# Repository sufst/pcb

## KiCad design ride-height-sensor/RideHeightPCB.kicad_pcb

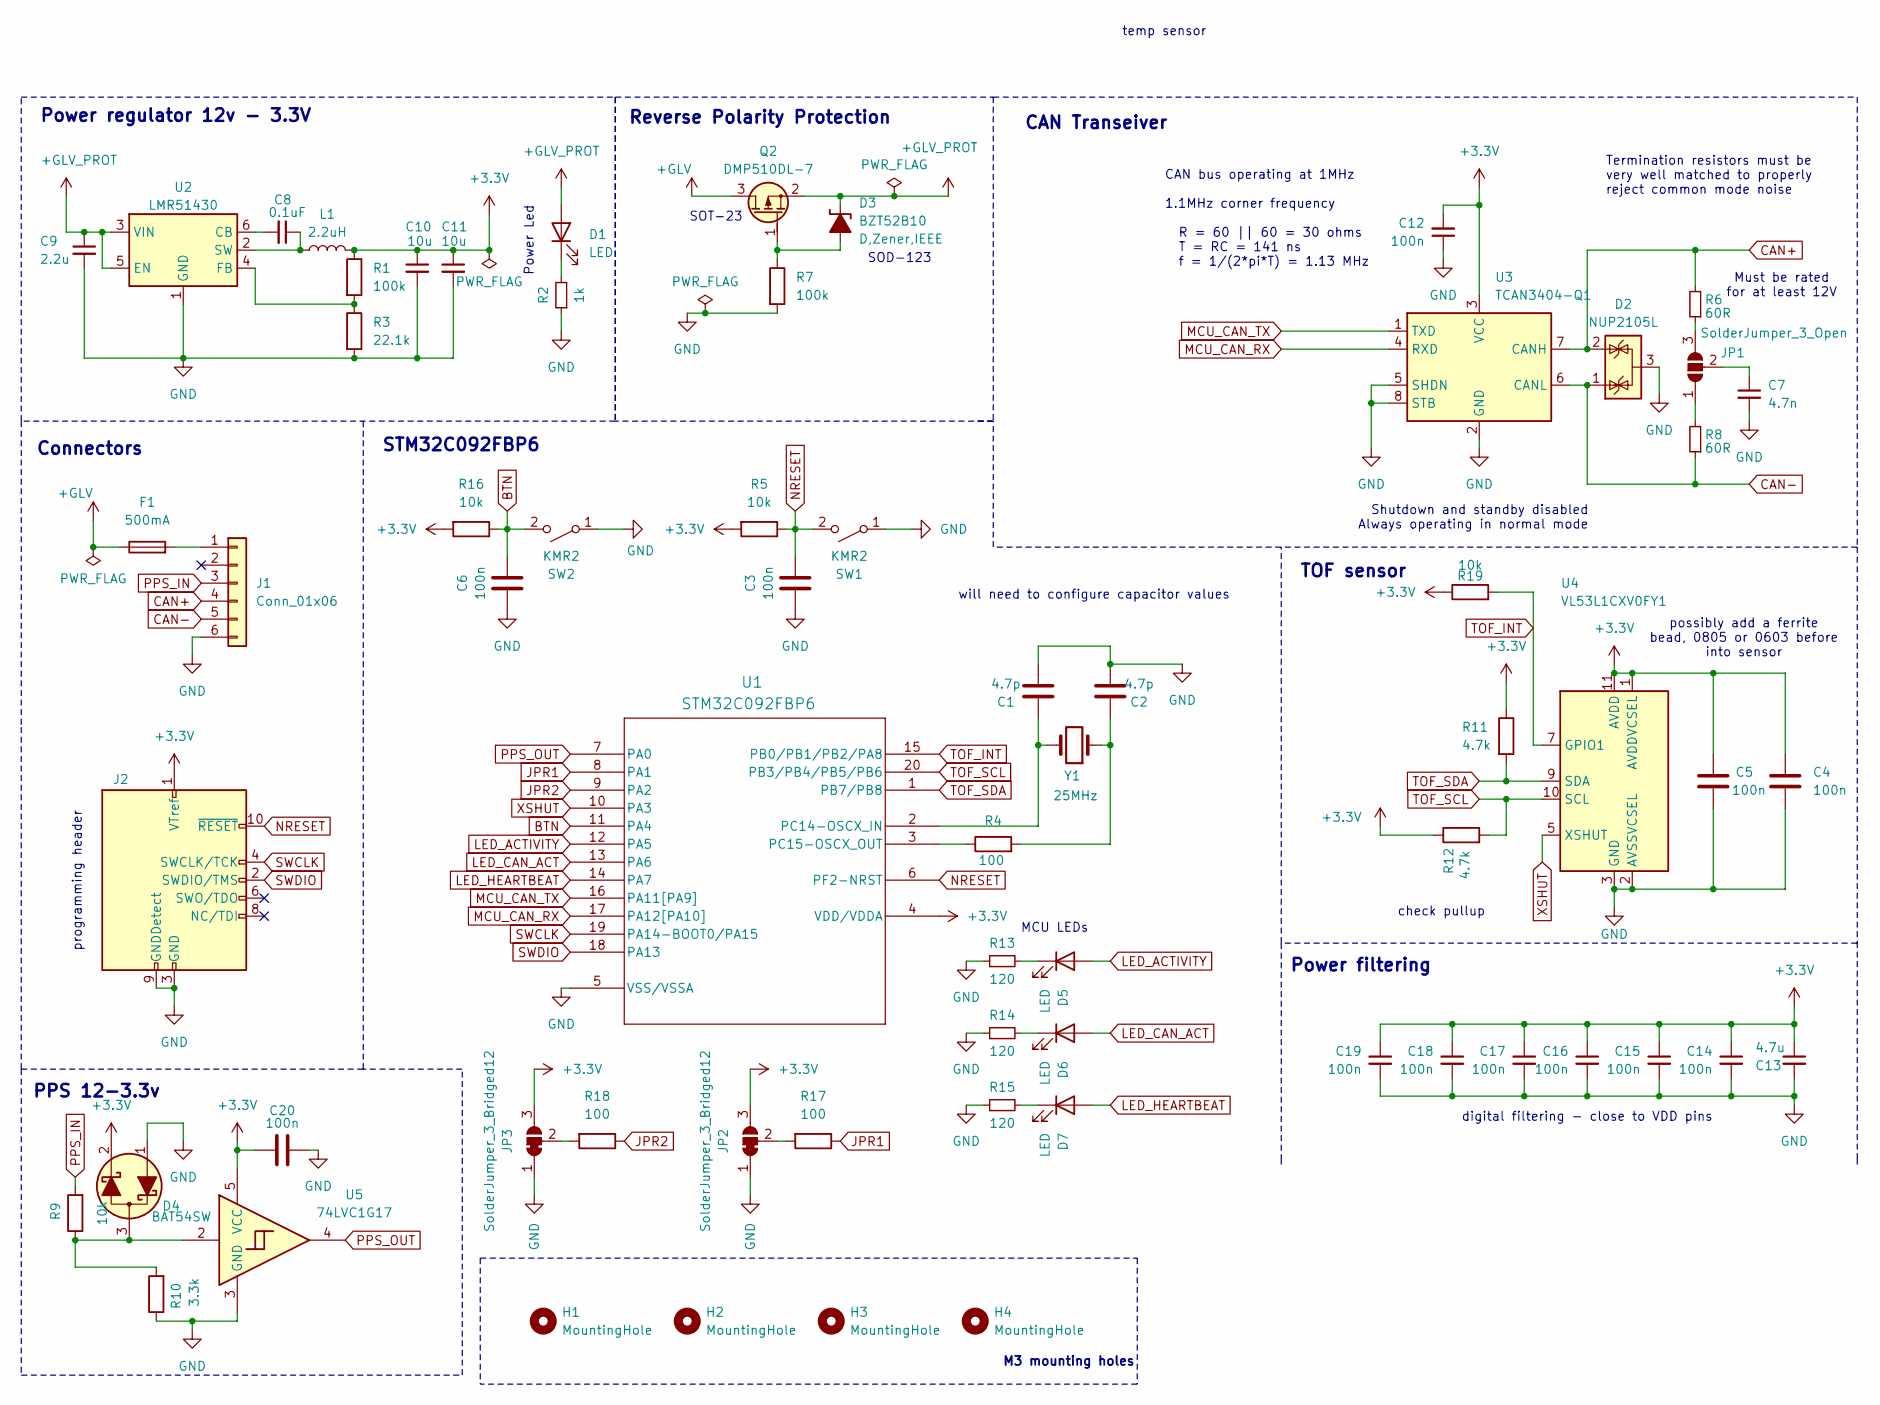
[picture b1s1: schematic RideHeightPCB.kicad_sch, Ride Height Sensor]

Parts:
C1, C2: 4.7p; C_0603_1608Metric_Pad1.08x0.95mm_HandSolder
C3, C4, C5, C6, C12, C14, C15, C16, C17, C18, C19, C20: 100n; C_0603_1608Metric_Pad1.08x0.95mm_HandSolder
C7: 4.7n; C_0603_1608Metric_Pad1.08x0.95mm_HandSolder
C8: 0.1uF; C_0603_1608Metric_Pad1.08x0.95mm_HandSolder
C9: 2.2u; C_0603_1608Metric_Pad1.08x0.95mm_HandSolder
C10: 10u; C_0805_2012Metric_Pad1.18x1.45mm_HandSolder
C11: 10u; C_0603_1608Metric_Pad1.08x0.95mm_HandSolder
C13: 4.7u; C_0603_1608Metric_Pad1.08x0.95mm_HandSolder
D1, D5, D6, D7: LED; LED_0805_2012Metric_Pad1.15x1.40mm_HandSolder
D2: NUP2105L; SOT-23; MPN NUP2105L
D3: BZT52B10; D_SOD-123; MPN BZT52B10
D4: BAT54SW; SOT-323_SC-70
F1: 500mA; Fuse_0603_1608Metric_Pad1.05x0.95mm_HandSolder
H1, H2, H3, H4: MountingHole; MountingHole_3.2mm_M3
J1: Conn_01x06; Molex_Micro-Fit_3.0_43650-0600_1x06_P3.00mm_Horizontal
J2: SHF10501LDSMLC; Mouser Order Number 200-SHF10501LDSMLC
JP1: SolderJumper_3_Open; SolderJumper-3_P1.3mm_Open_RoundedPad1.0x1.5mm
JP2, JP3: SolderJumper_3_Bridged12; SolderJumper-3_P1.3mm_Open_RoundedPad1.0x1.5mm
L1: 2.2uH; L_Coilcraft_XAL4020-XXX; MPN XAL4020-222MEC
Q2: DMP510DL-7; SOT-23
R1, R7: 100k; R_0603_1608Metric_Pad0.98x0.95mm_HandSolder
R2: 1k; R_0603_1608Metric_Pad0.98x0.95mm_HandSolder
R3: 22.1k; R_0603_1608Metric_Pad0.98x0.95mm_HandSolder
R4, R17, R18: 100; R_0603_1608Metric_Pad0.98x0.95mm_HandSolder
R5, R9, R16, R19: 10k; R_0603_1608Metric_Pad0.98x0.95mm_HandSolder
R6, R8: 60R; R_0603_1608Metric_Pad0.98x0.95mm_HandSolder
R10: 3.3k; R_0603_1608Metric_Pad0.98x0.95mm_HandSolder
R11, R12: 4.7k; R_0603_1608Metric_Pad0.98x0.95mm_HandSolder
R13, R14, R15: 120; R_0603_1608Metric_Pad0.98x0.95mm_HandSolder
SW1, SW2: KMR2; SW_Push_1P1T_NO_CK_KMR2; MPN KMR221NG LFS
U1: STM32C092FBP6; TSSOP20_STM
U2: LMR51430; SOT-23-6; MPN LMR51430YDDCR
U3: TCAN3404-Q1; SOT-23-8_Handsoldering; MPN TCAN3404DDFRQ1
U4: VL53L1CXV0FY1; ST_VL53L1x
U5: 74LVC1G17; SOT-353_SC-70-5_Handsoldering
Y1: 25MHz; Resonator_SMD_ECS_ECX-1247Q_1.6x1.2x0.3mm

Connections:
+3.3V: C4.2, C5.2, C10.1, C11.1, C12.2, C13.1, C14.1, C15.1, C16.1, C17.1, C18.1, C19.1, C20.1, D4.2 (K), J2.1 (VTref), JP2.3 (B), JP3.3 (B), L1.2, R1.1, R5.2, R11.1, R12.1, R16.2, R19.1, U1.4 (VDD/VDDA), U3.3 (VCC), U4.1 (AVDDVCSEL), U4.11 (AVDD), U5.5 (VCC)
+GLV: F1.1, Q2.3 (D); also elsewhere on the board
+GLV_PROT: C9.1, D1.2 (A), D3.1 (K-), Q2.2 (S), U2.3 (VIN), U2.5 (EN); also elsewhere on the board
BTN: C6.1, R16.1, SW2.2 (B), U1.11 (PA4)
CAN+: D2.2 (K), J1.4, R6.2, U3.7 (CANH)
CAN-: D2.1 (K), J1.5, R8.1, U3.6 (CANL)
JPR1: R17.1, U1.8 (PA1)
JPR2: R18.1, U1.9 (PA2)
LED_ACTIVITY: D5.2 (A), U1.12 (PA5)
LED_CAN_ACT: D6.2 (A), U1.13 (PA6)
LED_HEARTBEAT: D7.2 (A), U1.14 (PA7)
MCU_CAN_RX: U1.17 (PA12[PA10]), U3.4 (RXD)
MCU_CAN_TX: U1.16 (PA11[PA9]), U3.1 (TXD)
NRESET: C3.1, J2.10 (~RESET), R5.1, SW1.2 (B), U1.6 (PF2-NRST)
unnamed: D1.1 (K), R2.2
unnamed 15: D3.2 (A+), Q2.1 (G), R7.1; also elsewhere on the board
unnamed: D4.3 (C), R9.1, R10.2, U5.2
unnamed: D5.1 (K), R13.2
unnamed: D6.1 (K), R14.2
unnamed: D7.1 (K), R15.2
unnamed: F1.2, J1.1
unnamed: JP1.1 (A), R8.2
unnamed: JP1.3 (B), R6.1
unnamed: C7.1, JP1.2 (C)
unnamed: JP2.2 (C), R17.2
unnamed: JP3.2 (C), R18.2
unnamed: R4.1, U1.3 (PC15-OSCX_OUT)
unnamed: C8.2, U2.6 (CB)
unnamed: R1.2, R3.1, U2.4 (FB)
unnamed: C8.1, L1.1, U2.2 (SW)
PPS_IN: J1.3, R9.2
PPS_OUT: U1.7 (PA0), U5.4
SWCLK: J2.4 (SWCLK/TCK), U1.19 (PA14-BOOT0/PA15)
SWDIO: J2.2 (SWDIO/TMS), U1.18 (PA13)
TOF_INT: R19.2, U1.15 (PB0/PB1/PB2/PA8), U4.7 (GPIO1)
TOF_SCL: R12.2, U1.20 (PB3/PB4/PB5/PB6), U4.10 (SCL)
TOF_SDA: R11.2, U1.1 (PB7/PB8), U4.9 (SDA)
XSHUT: U1.10 (PA3), U4.5 (XSHUT)

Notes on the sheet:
PPS 12-3.3v
SOD-123
Termination resistors must be very well matched to properly reject common mode noise
CAN bus operating at 1MHz 1.1MHz corner frequency R = 60 || 60 = 30 ohms T = RC = 141 ns f = 1/(2*pi*T) = 1.13 MHz
Reverse Polarity Protection
Power filtering
will need to configure capacitor values
STM32C092FBP6
temp sensor
TOF sensor
Power regulator 12v - 3.3V
CAN Transeiver
MCU LEDs
programming header
check pullup
Connectors
SOT-23
digital filtering - close to VDD pins
M3 mounting holes
Must be rated for at least 12V
possibly add a ferrite bead, 0805 or 0603 before into sensor
Shutdown and standby disabled Always operating in normal mode
Power Led

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
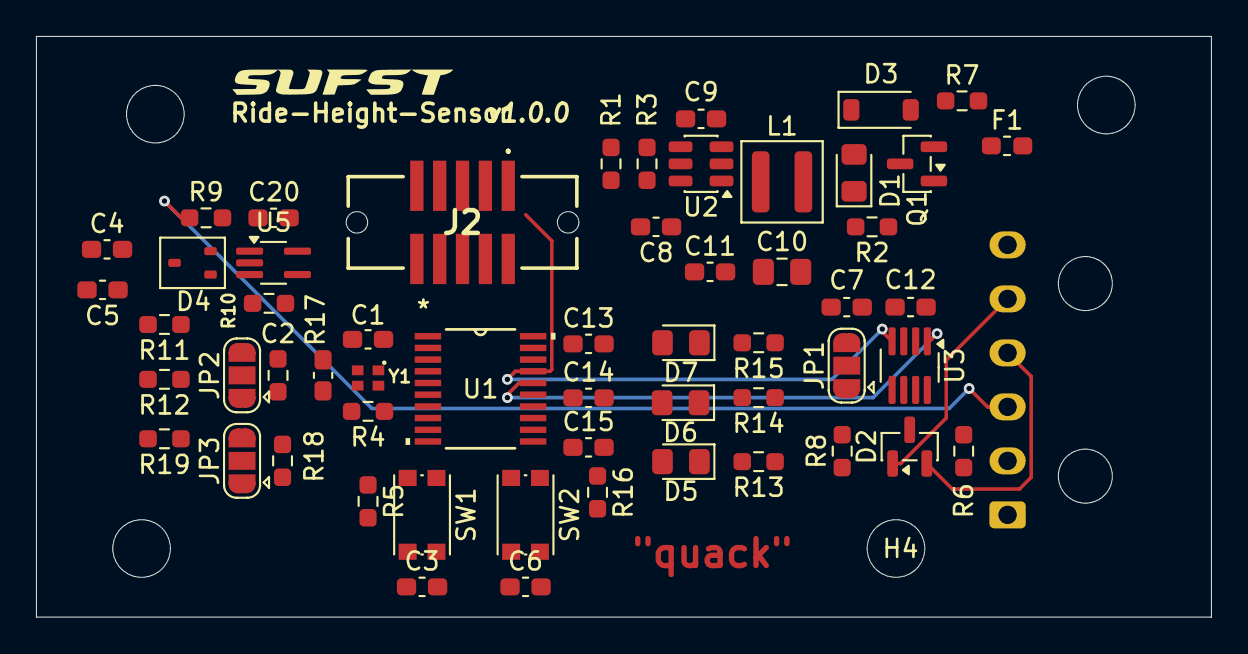
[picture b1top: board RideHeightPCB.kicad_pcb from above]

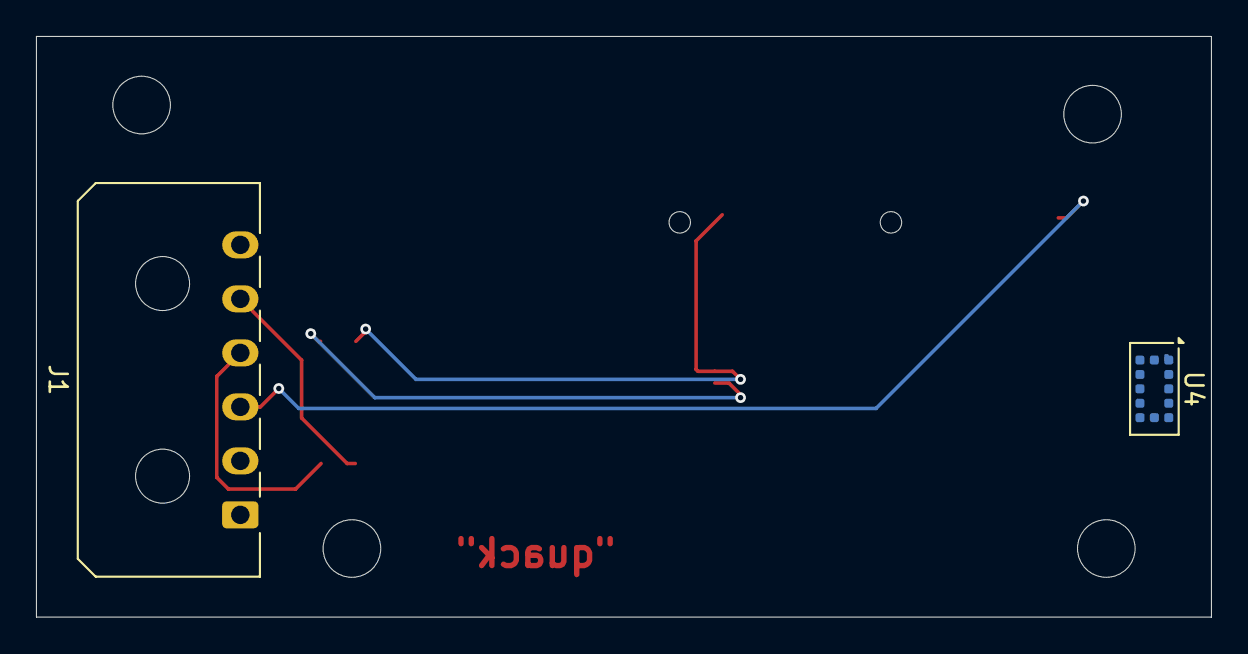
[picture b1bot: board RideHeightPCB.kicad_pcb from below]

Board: 4 copper layers, 65.3 x 32.3 mm, 62 parts (2 on the bottom side), 41 nets.

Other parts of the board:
Q1: DMP510DL-7; SOT-23

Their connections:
+GLV: Q1.1 (D); also elsewhere on the board
+GLV_PROT: Q1.3 (S); also elsewhere on the board
unnamed 15: Q1.2 (G); also elsewhere on the board

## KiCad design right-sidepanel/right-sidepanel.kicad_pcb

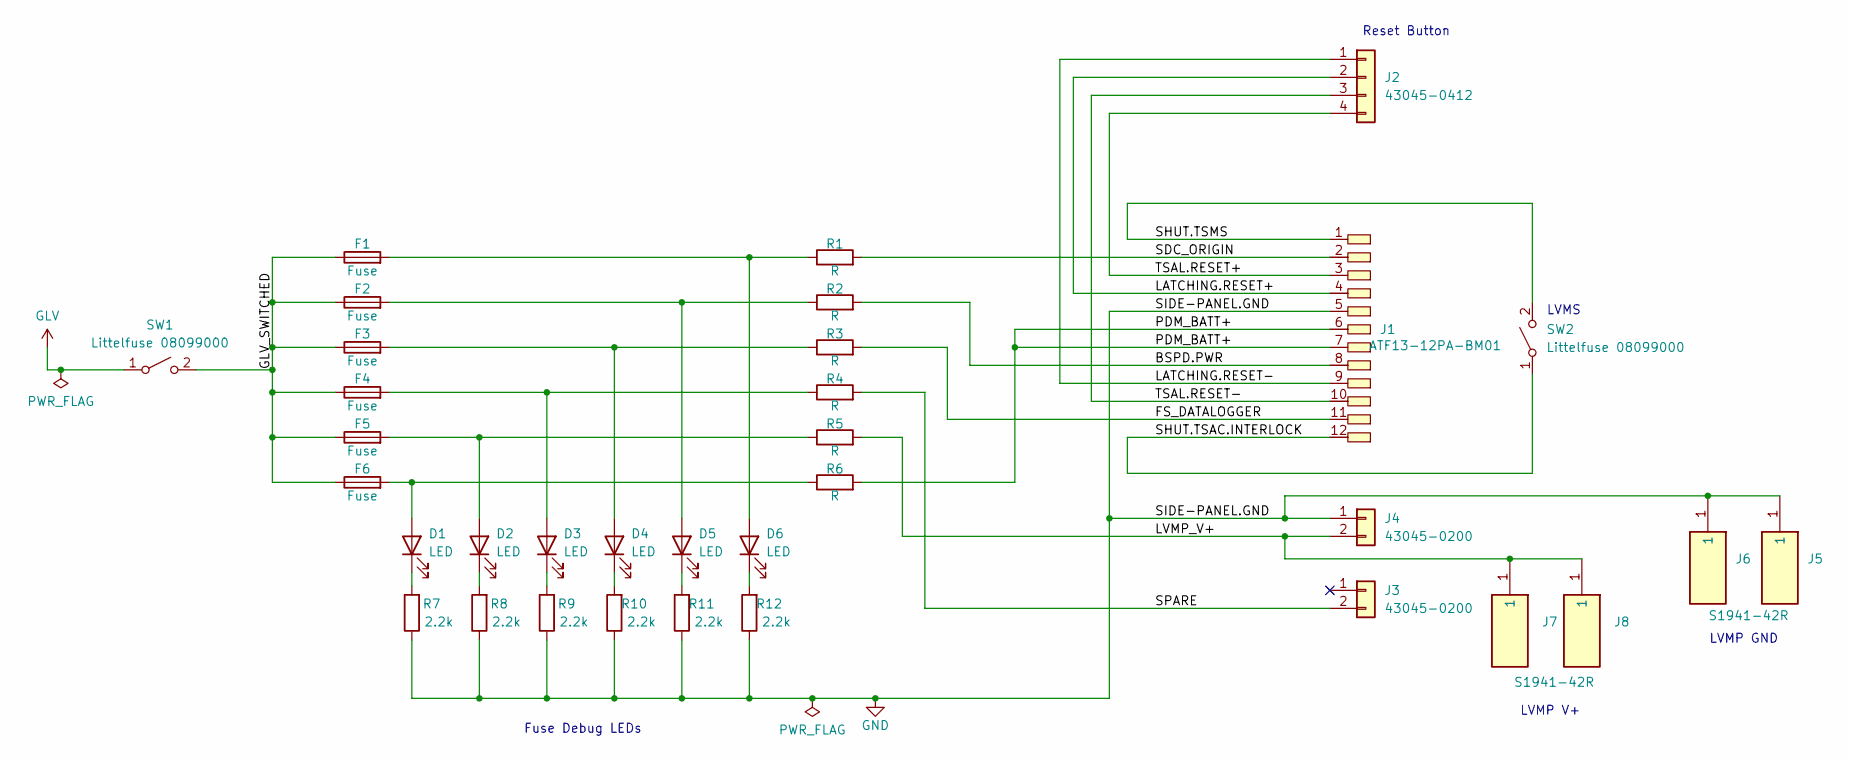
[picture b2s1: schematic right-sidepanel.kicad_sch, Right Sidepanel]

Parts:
D1, D2, D3, D4, D5, D6: LED; LED_0603_1608Metric
F1, F2, F3, F4, F5, F6: Fuse; 01000066Z
J1: ATF13-12PA-BM01; ATF1312PABM01
J2: 43045-0412; Molex_Micro-Fit_3.0_43045-0412_2x02_P3.00mm_Vertical
J3, J4: 43045-0200; Molex_Micro-Fit_3.0_43045-0200_2x01_P3.00mm_Horizontal
J5, J6, J7, J8: S1941-42R; S194142R_THT_secured; Mouser Part Number 855-S1941-42R
R1, R2, R3, R4, R5, R6: R; R_2512_6332Metric
R7, R8, R9, R10, R11, R12: 2.2k; R_0603_1608Metric
SW1, SW2: Littelfuse 08099000

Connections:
/BSPD.PWR: J1.8, R2.2
/FS_DATALOGGER: J1.11, R3.2
/GLV_SWITCHED: F1.1, F2.1, F3.1, F4.1, F5.1, F6.1, SW1.2 (B)
/LATCHING.RESET+: J1.4, J2.2
/LATCHING.RESET-: J1.9, J2.1
/LVMP_V+: J4.2, J7.1, J8.1, R5.2
/PDM_BATT+: J1.6, J1.7, R6.2
/SDC_ORIGIN: J1.2, R1.2
/SHUT.TSAC.INTERLOCK: J1.12, SW2.1 (A)
/SHUT.TSMS: J1.1, SW2.2 (B)
/SIDE-PANEL.GND: J1.5, J4.1, J5.1, J6.1, R7.1, R8.1, R9.1, R10.1, R11.1, R12.1
/SPARE: J3.2, R4.2
/TSAL.RESET+: J1.3, J2.4
/TSAL.RESET-: J1.10, J2.3
GLV: SW1.1 (A)
unnamed: D1.2 (A), F6.2, R6.1
unnamed: D1.1 (K), R7.2
unnamed: D2.2 (A), F5.2, R5.1
unnamed: D2.1 (K), R8.2
unnamed: D3.2 (A), F4.2, R4.1
unnamed: D3.1 (K), R9.2
unnamed: D4.2 (A), F3.2, R3.1
unnamed: D4.1 (K), R10.2
unnamed: D5.2 (A), F2.2, R2.1
unnamed: D5.1 (K), R11.2
unnamed: D6.2 (A), F1.2, R1.1
unnamed: D6.1 (K), R12.2

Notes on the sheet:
Fuse Debug LEDs
LVMP GND
LVMS
Reset Button
LVMP V+

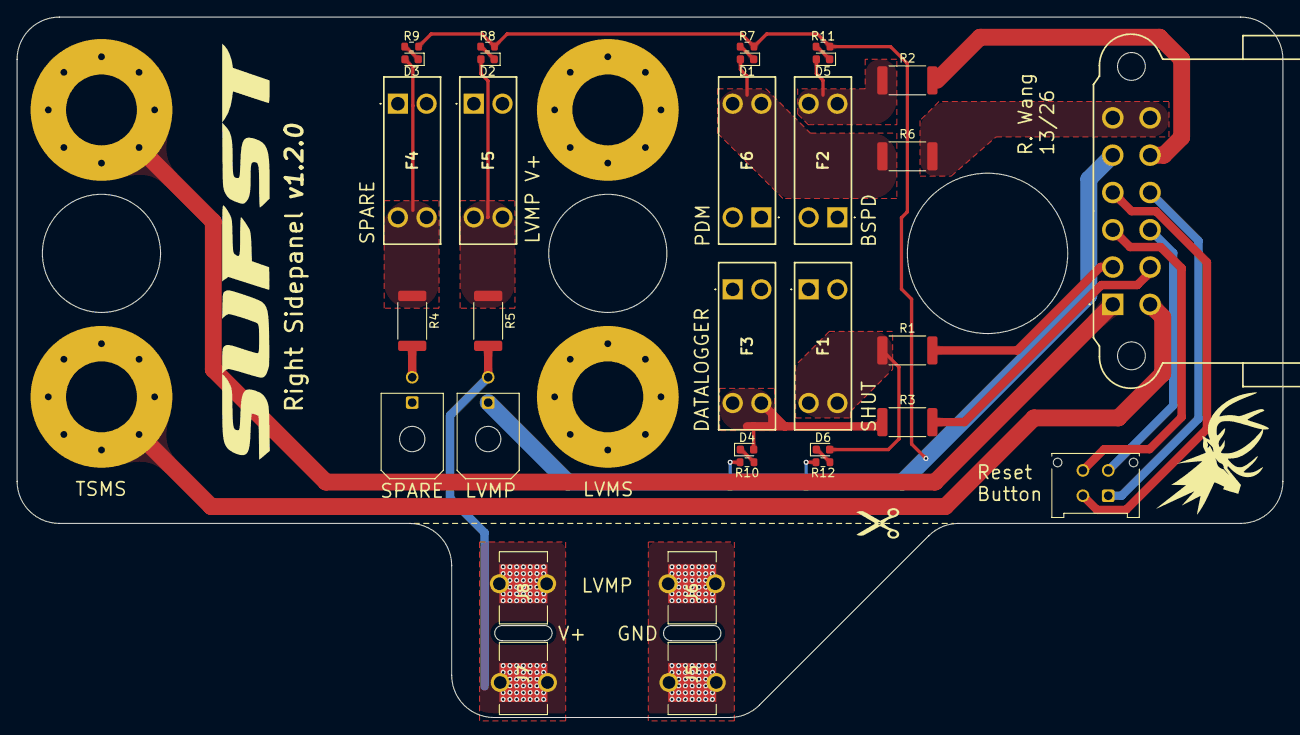
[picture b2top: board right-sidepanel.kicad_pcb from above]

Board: 2 copper layers, 150.0 x 83.0 mm, 34 parts (0 on the bottom side), 26 nets.

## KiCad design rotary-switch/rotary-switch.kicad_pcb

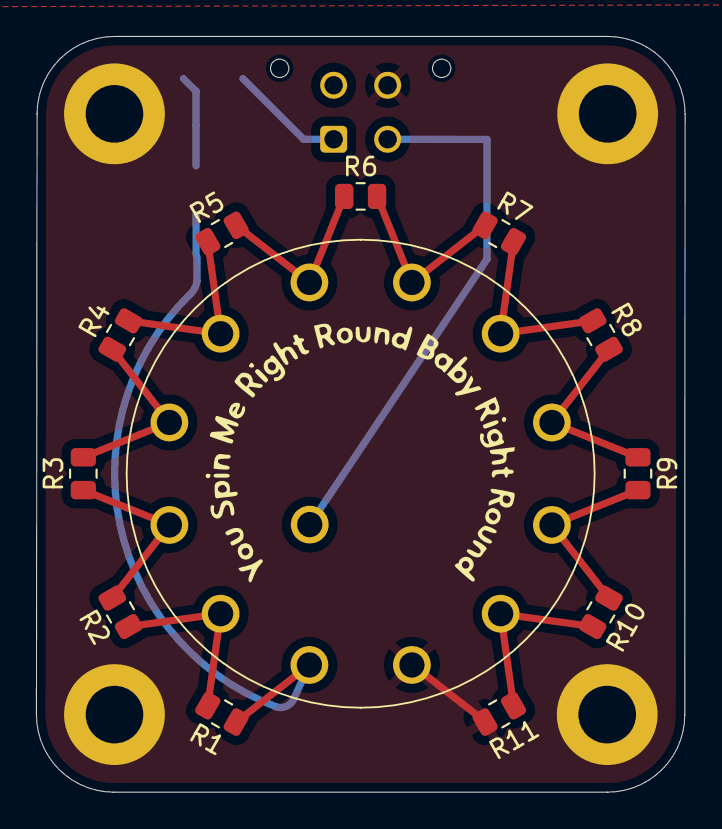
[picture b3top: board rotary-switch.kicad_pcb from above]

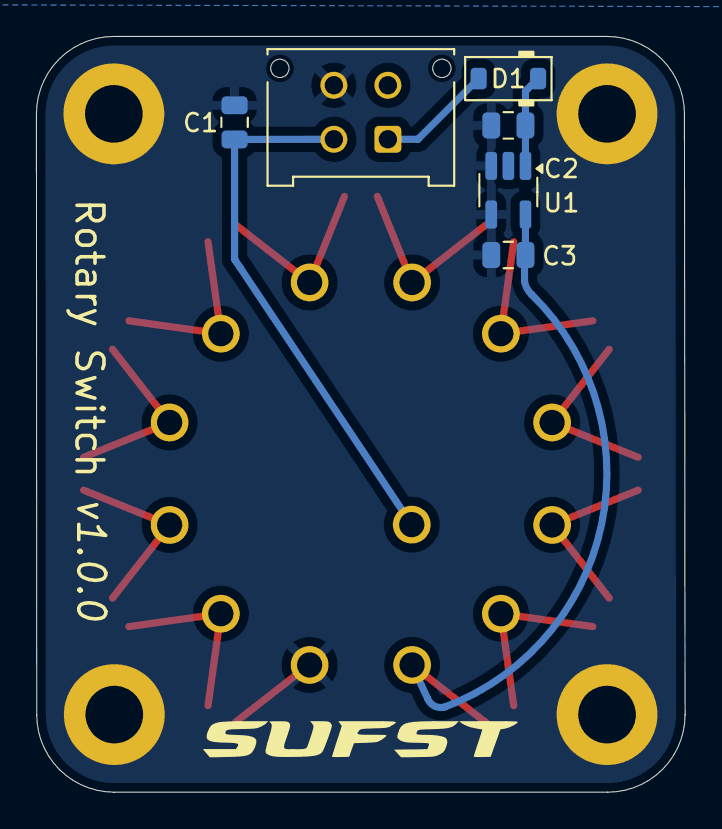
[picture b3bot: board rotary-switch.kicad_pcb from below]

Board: 2 copper layers, 36.0 x 42.0 mm, 22 parts (6 on the bottom side), 15 nets.

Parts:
C1: 1u; C_0805_2012Metric
C2: 10uF; C_0805_2012Metric
C3: 4.7uF; C_0805_2012Metric
D1: 1N5711W; D_SOD-123
H1, H2, H3, H4: MountingHole_Pad; MountingHole_3.2mm_M3_DIN965_Pad
J1: Conn_01x04_Socket; Molex_Micro-Fit_3.0_43045-0412_2x02_P3.00mm_Vertical
R1, R2, R3, R4, R5, R6, R7, R8, R9, R10, R11: 330; R_0805_2012Metric
SW1: SW_Rotary_1x12; ALPHA_12pos_rotary
U1: TPS7B6925-Q1; SOT-23-5_HandSoldering

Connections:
+3V3: C3.1, R1.1, SW1.1, U1.5 (OUT)
+GLV: D1.2 (A), J1.1
/Output: C1.1, J1.2, SW1.13
GND: C1.2, C2.2, C3.2, H1.1, H2.1, H3.1, H4.1, J1.4, R11.2, SW1.12, U1.3 (GND), U1.4 (GND)
unnamed: C2.1, D1.1 (K), U1.1 (IN)
unnamed: R1.2, R2.1, SW1.2
unnamed: R2.2, R3.1, SW1.3
unnamed: R3.2, R4.1, SW1.4
unnamed: R4.2, R5.1, SW1.5
unnamed: R5.2, R6.1, SW1.6
unnamed: R6.2, R7.1, SW1.7
unnamed: R7.2, R8.1, SW1.8
unnamed: R8.2, R9.1, SW1.9
unnamed: R9.2, R10.1, SW1.10
unnamed: R10.2, R11.1, SW1.11

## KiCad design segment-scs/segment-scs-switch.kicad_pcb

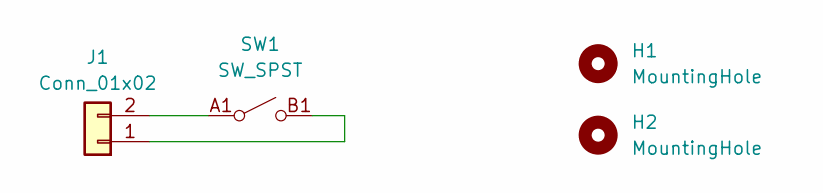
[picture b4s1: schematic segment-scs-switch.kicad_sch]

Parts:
H1, H2: MountingHole; MountingHole_3.2mm_M3
J1: Conn_01x02; Conn2_SMD
SW1: SW_SPST; 24549852

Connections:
unnamed: J1.1, SW1.B1 (B)
unnamed: J1.2, SW1.A1 (A)

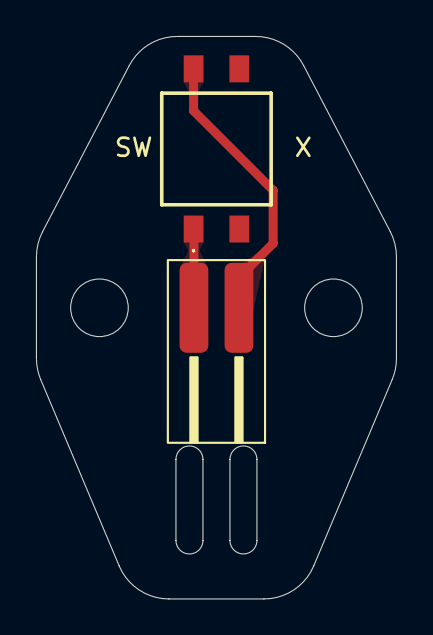
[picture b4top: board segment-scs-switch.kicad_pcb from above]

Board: 2 copper layers, 20.0 x 31.2 mm, 4 parts (0 on the bottom side), 2 nets.

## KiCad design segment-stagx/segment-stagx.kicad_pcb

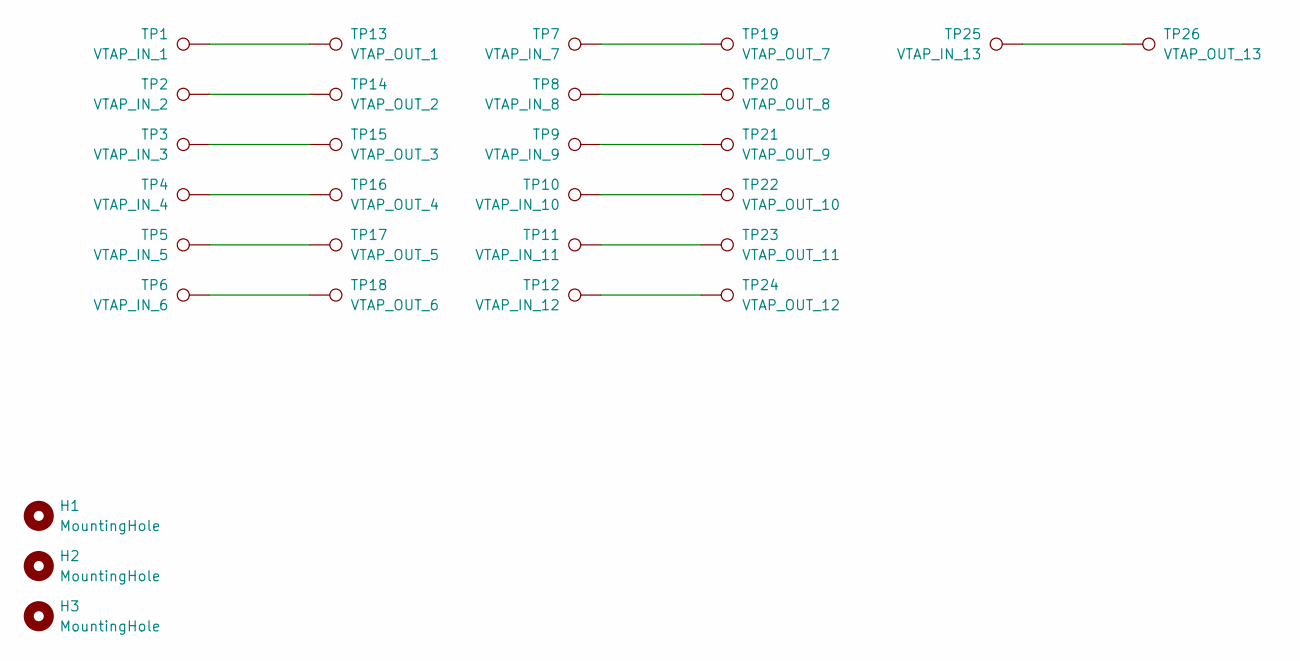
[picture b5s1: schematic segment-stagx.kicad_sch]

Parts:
H1, H2, H3: MountingHole; Segment_Thermistor_Tyrap
TP1: VTAP_IN_1; Segment_Voltage_Tap_Positive
TP2: VTAP_IN_2; Segment_Voltage_Tap
TP3: VTAP_IN_3; Segment_Voltage_Tap
TP4: VTAP_IN_4; Segment_Voltage_Tap
TP5: VTAP_IN_5; Segment_Voltage_Tap
TP6: VTAP_IN_6; Segment_Voltage_Tap
TP7: VTAP_IN_7; Segment_Voltage_Tap
TP8: VTAP_IN_8; Segment_Voltage_Tap
TP9: VTAP_IN_9; Segment_Voltage_Tap
TP10: VTAP_IN_10; Segment_Voltage_Tap
TP11: VTAP_IN_11; Segment_Voltage_Tap
TP12: VTAP_IN_12; Segment_Voltage_Tap
TP13: VTAP_OUT_1; 55A_24AWG_Solder
TP14: VTAP_OUT_2; 55A_24AWG_Solder
TP15: VTAP_OUT_3; 55A_24AWG_Solder
TP16: VTAP_OUT_4; 55A_24AWG_Solder
TP17: VTAP_OUT_5; 55A_24AWG_Solder
TP18: VTAP_OUT_6; 55A_24AWG_Solder
TP19: VTAP_OUT_7; 55A_24AWG_Solder
TP20: VTAP_OUT_8; 55A_24AWG_Solder
TP21: VTAP_OUT_9; 55A_24AWG_Solder
TP22: VTAP_OUT_10; 55A_24AWG_Solder
TP23: VTAP_OUT_11; 55A_24AWG_Solder
TP24: VTAP_OUT_12; 55A_24AWG_Solder
TP25: VTAP_IN_13; Segment_Voltage_Tap_Negative
TP26: VTAP_OUT_13; 55A_24AWG_Solder

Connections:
unnamed: TP1.1, TP13.1
unnamed: TP10.1, TP22.1
unnamed: TP11.1, TP23.1
unnamed: TP12.1, TP24.1
unnamed: TP2.1, TP14.1
unnamed: TP3.1, TP15.1
unnamed: TP4.1, TP16.1
unnamed: TP5.1, TP17.1
unnamed: TP6.1, TP18.1
unnamed: TP7.1, TP19.1
unnamed: TP8.1, TP20.1
unnamed: TP9.1, TP21.1
unnamed: TP25.1, TP26.1

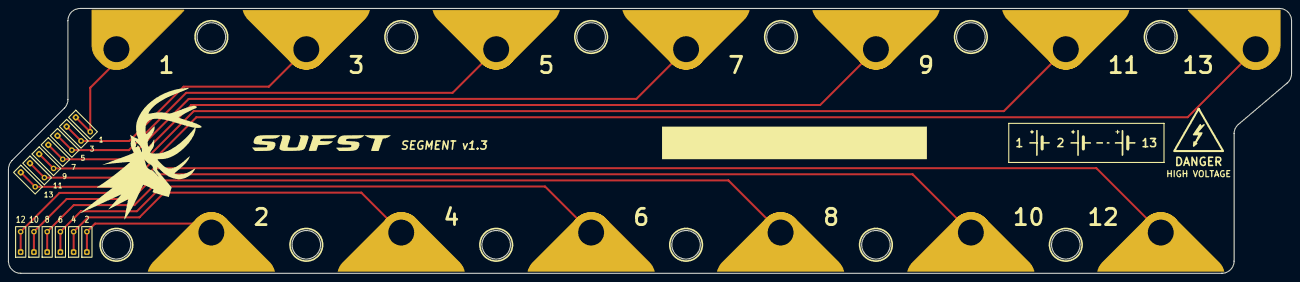
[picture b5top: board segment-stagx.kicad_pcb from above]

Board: 2 copper layers, 314.9 x 65.0 mm, 29 parts (0 on the bottom side), 13 nets.

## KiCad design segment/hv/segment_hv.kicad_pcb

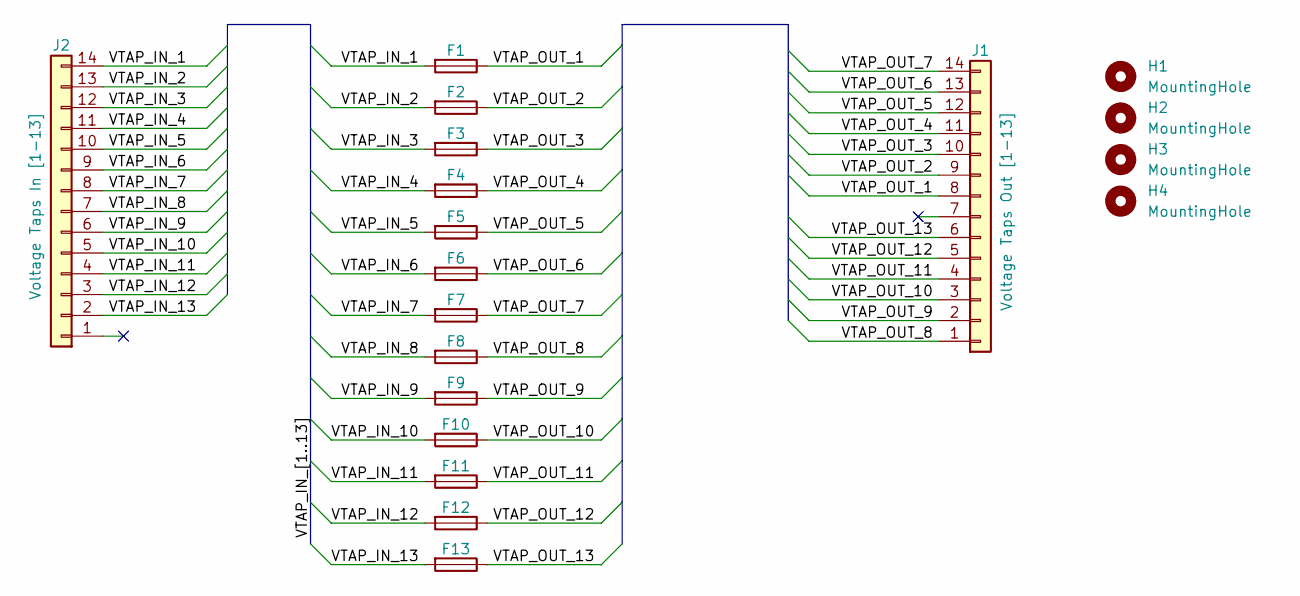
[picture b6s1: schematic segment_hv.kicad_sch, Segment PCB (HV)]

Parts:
F1, F2, F3, F4, F5, F6, F7, F8, F9, F10, F11, F12, F13: Fuse; Littelfuse-04611-25ER
H1, H2, H3, H4: MountingHole; MountingHole_4.3mm_M4
J1: Voltage Taps Out [1-13]; Molex_Micro-Fit_3.0_43045-1400_2x07_P3.00mm_Horizontal
J2: Voltage Taps In [1-13]; Molex_Micro-Fit_3.0_43045-1412_2x07_P3.00mm_Vertical

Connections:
/VTAP_IN_1: F1.2, J2.14
/VTAP_IN_2: F2.2, J2.13
/VTAP_IN_3: F3.2, J2.12
/VTAP_IN_4: F4.2, J2.11
/VTAP_IN_5: F5.2, J2.10
/VTAP_IN_6: F6.2, J2.9
/VTAP_IN_7: F7.2, J2.8
/VTAP_IN_8: F8.2, J2.7
/VTAP_IN_9: F9.2, J2.6
/VTAP_IN_10: F10.2, J2.5
/VTAP_IN_11: F11.2, J2.4
/VTAP_IN_12: F12.2, J2.3
/VTAP_IN_13: F13.2, J2.2
/VTAP_OUT_1: F1.1, J1.8
/VTAP_OUT_2: F2.1, J1.9
/VTAP_OUT_3: F3.1, J1.10
/VTAP_OUT_4: F4.1, J1.11
/VTAP_OUT_5: F5.1, J1.12
/VTAP_OUT_6: F6.1, J1.13
/VTAP_OUT_7: F7.1, J1.14
/VTAP_OUT_8: F8.1, J1.1
/VTAP_OUT_9: F9.1, J1.2
/VTAP_OUT_10: F10.1, J1.3
/VTAP_OUT_11: F11.1, J1.4
/VTAP_OUT_12: F12.1, J1.5
/VTAP_OUT_13: F13.1, J1.6

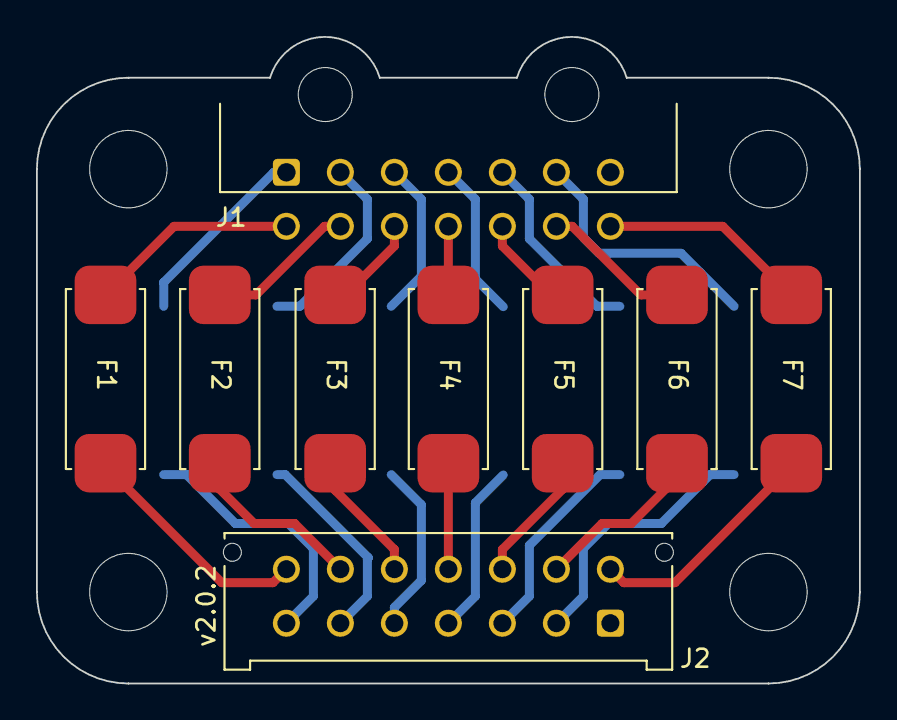
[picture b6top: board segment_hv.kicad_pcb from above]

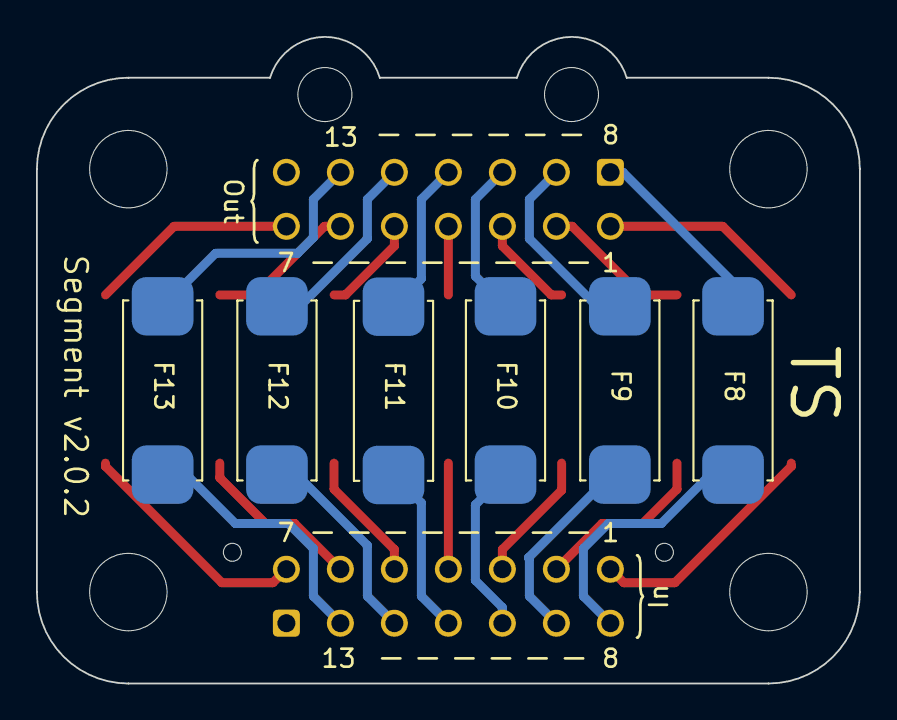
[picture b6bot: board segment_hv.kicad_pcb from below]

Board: 2 copper layers, 45.7 x 35.9 mm, 19 parts (6 on the bottom side), 26 nets.

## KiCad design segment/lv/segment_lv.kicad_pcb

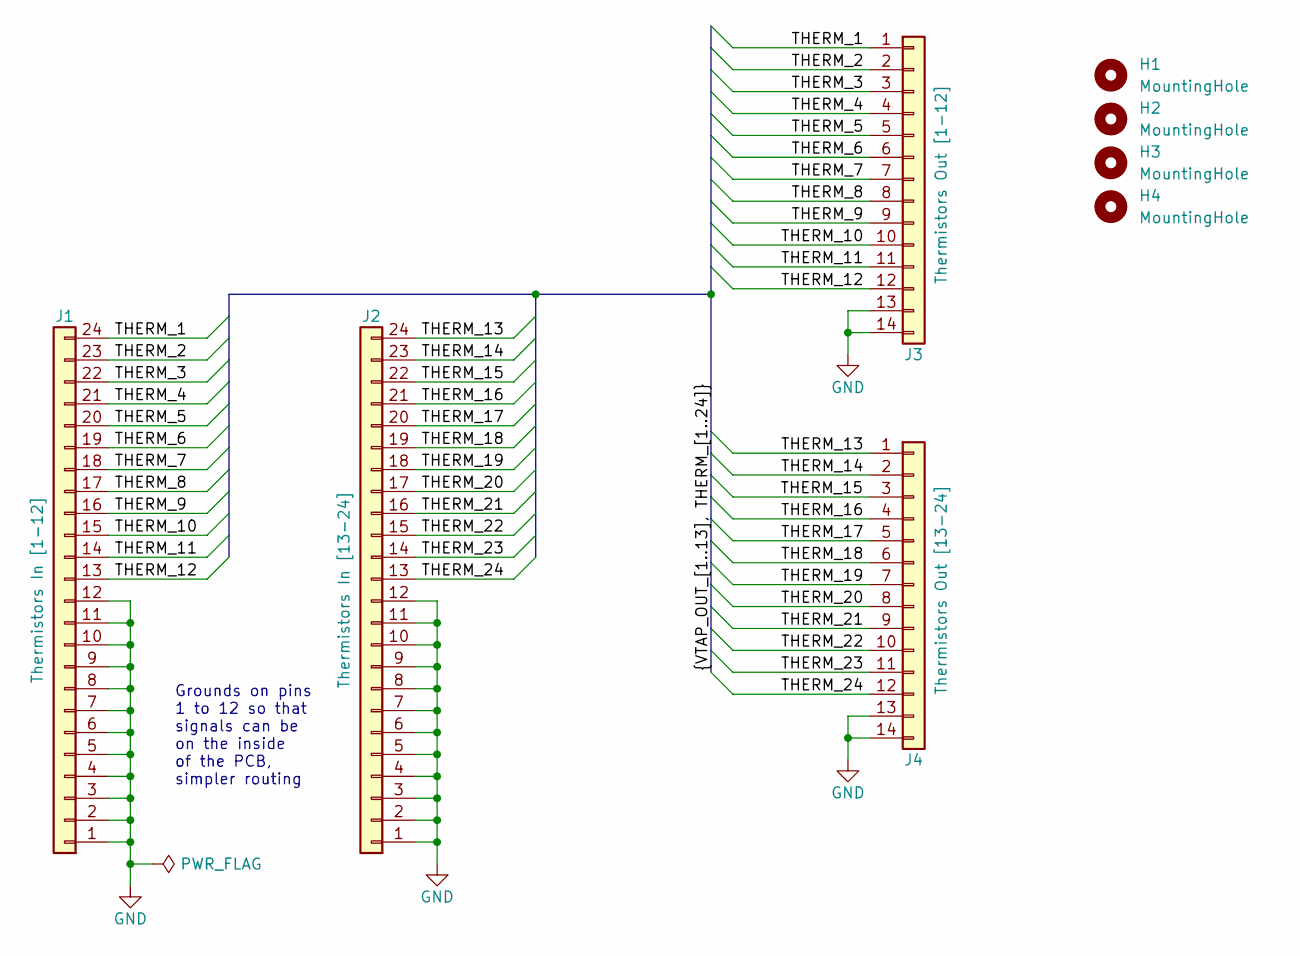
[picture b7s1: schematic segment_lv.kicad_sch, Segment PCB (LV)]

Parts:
H1, H2, H3, H4: MountingHole; MountingHole_4.3mm_M4
J1: Thermistors In [1-12]; Molex_Micro-Fit_3.0_43045-2400_2x12_P3.00mm_Horizontal
J2: Thermistors In [13-24]; Molex_Micro-Fit_3.0_43045-2400_2x12_P3.00mm_Horizontal
J3: Thermistors Out [1-12]; Molex_Micro-Fit_3.0_43045-1412_2x07_P3.00mm_Vertical
J4: Thermistors Out [13-24]; Molex_Micro-Fit_3.0_43045-1412_2x07_P3.00mm_Vertical

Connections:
/THERM_1: J1.24, J3.1
/THERM_2: J1.23, J3.2
/THERM_3: J1.22, J3.3
/THERM_4: J1.21, J3.4
/THERM_5: J1.20, J3.5
/THERM_6: J1.19, J3.6
/THERM_7: J1.18, J3.7
/THERM_8: J1.17, J3.8
/THERM_9: J1.16, J3.9
/THERM_10: J1.15, J3.10
/THERM_11: J1.14, J3.11
/THERM_12: J1.13, J3.12
/THERM_13: J2.24, J4.1
/THERM_14: J2.23, J4.2
/THERM_15: J2.22, J4.3
/THERM_16: J2.21, J4.4
/THERM_17: J2.20, J4.5
/THERM_18: J2.19, J4.6
/THERM_19: J2.18, J4.7
/THERM_20: J2.17, J4.8
/THERM_21: J2.16, J4.9
/THERM_22: J2.15, J4.10
/THERM_23: J2.14, J4.11
/THERM_24: J2.13, J4.12
GND: J1.1, J1.2, J1.3, J1.4, J1.5, J1.6, J1.7, J1.8, J1.9, J1.10, J1.11, J1.12, J2.1, J2.2, J2.3, J2.4, J2.5, J2.6, J2.7, J2.8, J2.9, J2.10, J2.11, J2.12, J3.13, J3.14, J4.13, J4.14

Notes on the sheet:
Grounds on pins 1 to 12 so that signals can be on the inside of the PCB, simpler routing

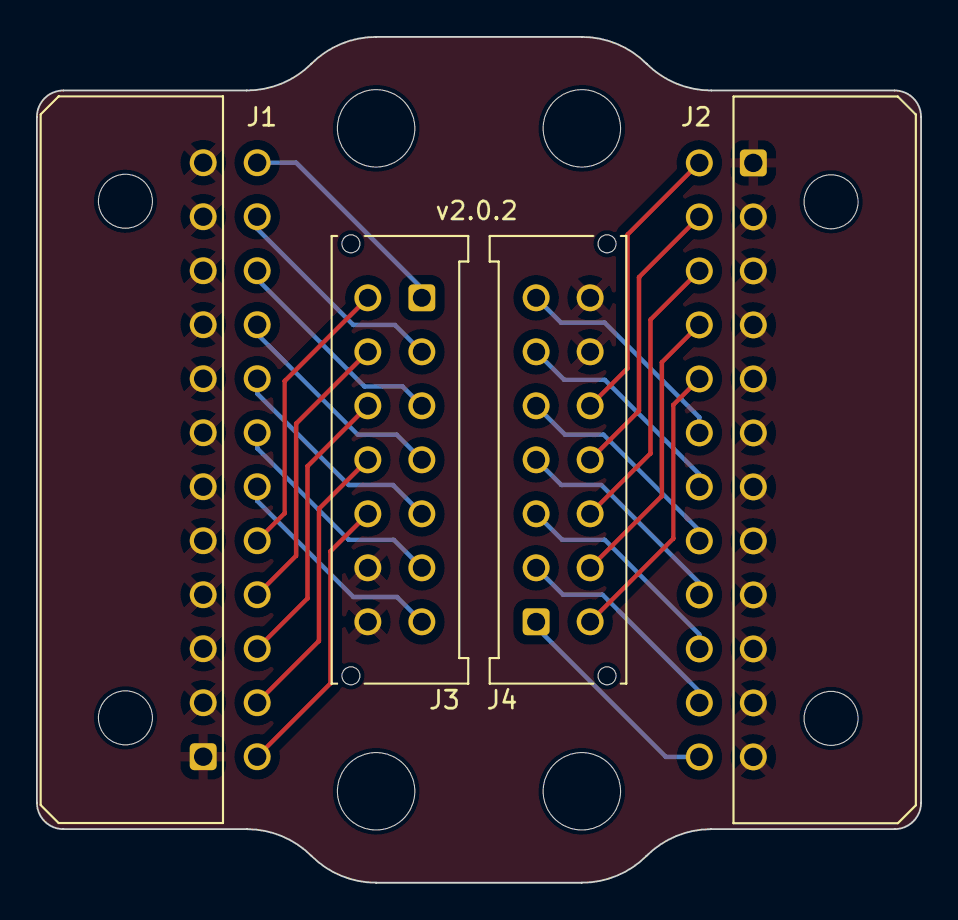
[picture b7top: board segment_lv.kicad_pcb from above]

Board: 2 copper layers, 49.1 x 47.0 mm, 8 parts (0 on the bottom side), 25 nets.

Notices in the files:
parts and their libraries:
License: Apache-2.0
